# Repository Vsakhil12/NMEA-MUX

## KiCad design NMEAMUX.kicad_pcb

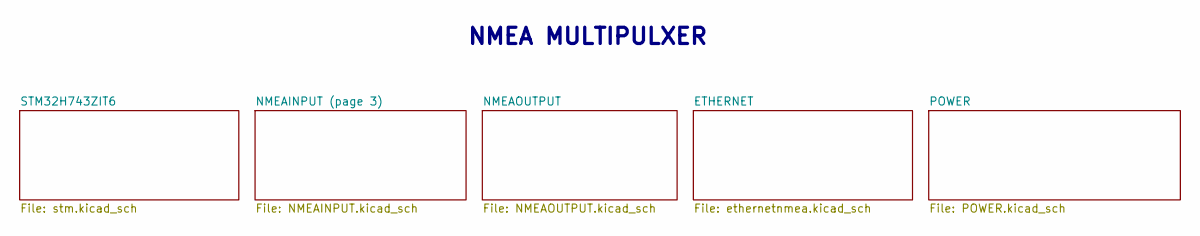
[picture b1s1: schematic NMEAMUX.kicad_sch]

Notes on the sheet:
NMEA MULTIPULXER

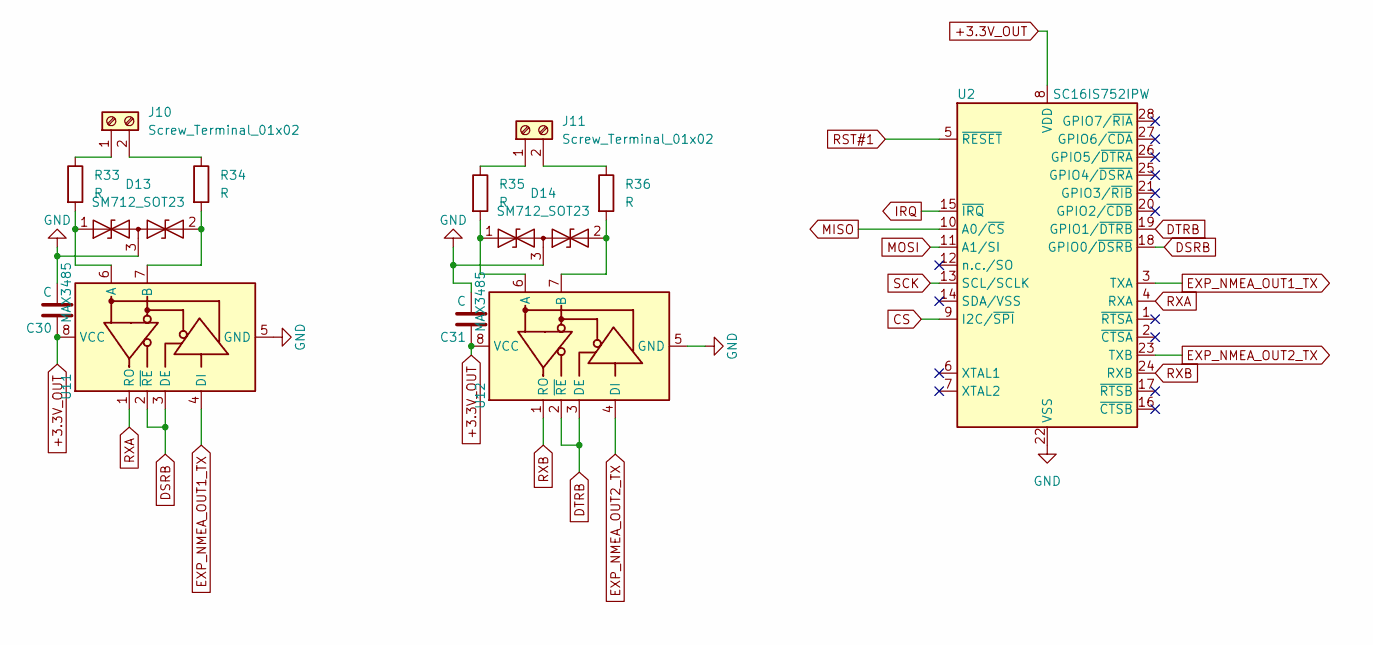
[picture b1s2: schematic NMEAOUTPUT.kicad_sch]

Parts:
C30, C31: C
D13, D14: SM712_SOT23; SOT-23
J10, J11: Screw_Terminal_01x02
R33, R34, R35, R36: R
U2: SC16IS752IPW; TSSOP-28_4.4x9.7mm_P0.65mm
U11, U12: MAX3485; SOIC-8_3.9x4.9mm_P1.27mm

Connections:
+3.3V_OUT: C30.1, C31.1, U2.8 (VDD), U11.8 (VCC), U12.8 (VCC); also elsewhere on the board
CS: U2.9 (I2C/~SPI); also elsewhere on the board
DSRB: U2.18 (GPIO0/~DSRB), U11.2 (~RE), U11.3 (DE)
DTRB: U2.19 (GPIO1/~DTRB), U12.2 (~RE), U12.3 (DE)
EXP_NMEA_OUT1_TX: U2.3 (TXA), U11.4 (DI)
EXP_NMEA_OUT2_TX: U2.23 (TXB), U12.4 (DI)
GND: C30.2, C31.2, D13.3 (common), D14.3 (common), U2.22 (VSS), U11.5 (GND), U12.5 (GND); also elsewhere on the board
IRQ: U2.15 (~IRQ); also elsewhere on the board
MISO: U2.10 (A0/~CS); also elsewhere on the board
MOSI: U2.11 (A1/SI); also elsewhere on the board
unnamed: D13.1 (A1), R33.2, U11.6 (A)
unnamed: D13.2 (A2), R34.2, U11.7 (B)
unnamed: D14.1 (A1), R35.2, U12.6 (A)
unnamed: D14.2 (A2), R36.2, U12.7 (B)
unnamed: J10.1, R33.1
unnamed: J10.2, R34.1
unnamed: J11.1, R35.1
unnamed: J11.2, R36.1
RST#1: U2.5 (~RESET); also elsewhere on the board
RXA: U2.4 (RXA), U11.1 (RO)
RXB: U2.24 (RXB), U12.1 (RO)
SCK: U2.13 (SCL/SCLK); also elsewhere on the board

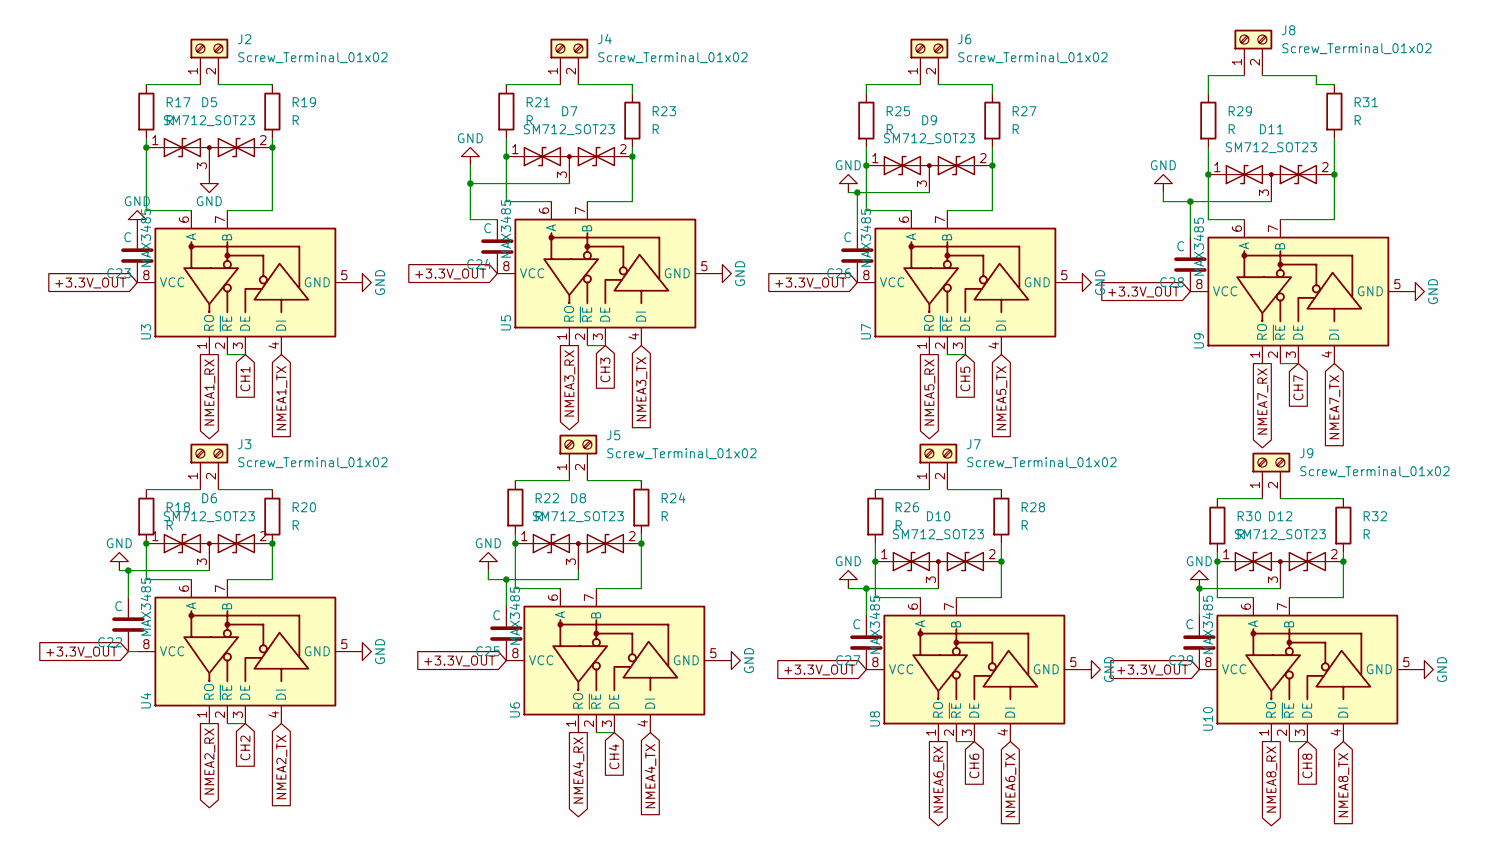
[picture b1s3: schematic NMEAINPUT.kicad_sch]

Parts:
C22, C23, C24, C25, C26, C27, C28, C29: C
D5, D6, D7, D8, D9, D10, D11, D12: SM712_SOT23; SOT-23
J2, J3, J4, J5, J6, J7, J8, J9: Screw_Terminal_01x02
R17, R18, R19, R20, R21, R22, R23, R24, R25, R26, R27, R28, R29, R30, R31, R32: R
U3, U4, U5, U6, U7, U8, U9, U10: MAX3485; SOIC-8_3.9x4.9mm_P1.27mm

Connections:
+3.3V_OUT: C22.1, C23.1, C24.1, C25.1, C26.1, C27.1, C28.1, C29.1, U3.8 (VCC), U4.8 (VCC), U5.8 (VCC), U6.8 (VCC), U7.8 (VCC), U8.8 (VCC), U9.8 (VCC), U10.8 (VCC); also elsewhere on the board
CH1: U3.2 (~RE), U3.3 (DE); also elsewhere on the board
CH2: U4.2 (~RE), U4.3 (DE); also elsewhere on the board
CH3: U5.2 (~RE), U5.3 (DE); also elsewhere on the board
CH4: U6.2 (~RE), U6.3 (DE); also elsewhere on the board
CH5: U7.2 (~RE), U7.3 (DE); also elsewhere on the board
CH6: U8.2 (~RE), U8.3 (DE); also elsewhere on the board
CH7: U9.2 (~RE), U9.3 (DE); also elsewhere on the board
CH8: U10.2 (~RE), U10.3 (DE); also elsewhere on the board
GND: C22.2, C23.2, C24.2, C25.2, C26.2, C27.2, C28.2, C29.2, D5.3 (common), D6.3 (common), D7.3 (common), D8.3 (common), D9.3 (common), D10.3 (common), D11.3 (common), D12.3 (common), U3.5 (GND), U4.5 (GND), U5.5 (GND), U6.5 (GND), U7.5 (GND), U8.5 (GND), U9.5 (GND), U10.5 (GND); also elsewhere on the board
NMEA1_RX: U3.1 (RO); also elsewhere on the board
NMEA1_TX: U3.4 (DI); also elsewhere on the board
NMEA2_RX: U4.1 (RO); also elsewhere on the board
NMEA2_TX: U4.4 (DI); also elsewhere on the board
NMEA3_RX: U5.1 (RO); also elsewhere on the board
NMEA3_TX: U5.4 (DI); also elsewhere on the board
NMEA4_RX: U6.1 (RO); also elsewhere on the board
NMEA4_TX: U6.4 (DI); also elsewhere on the board
NMEA5_RX: U7.1 (RO); also elsewhere on the board
NMEA5_TX: U7.4 (DI); also elsewhere on the board
NMEA6_RX: U8.1 (RO); also elsewhere on the board
NMEA6_TX: U8.4 (DI); also elsewhere on the board
NMEA7_RX: U9.1 (RO); also elsewhere on the board
NMEA7_TX: U9.4 (DI); also elsewhere on the board
NMEA8_RX: U10.1 (RO); also elsewhere on the board
NMEA8_TX: U10.4 (DI); also elsewhere on the board
unnamed: D5.1 (A1), R17.2, U3.6 (A)
unnamed: D5.2 (A2), R19.2, U3.7 (B)
unnamed: D6.1 (A1), R18.2, U4.6 (A)
unnamed: D6.2 (A2), R20.2, U4.7 (B)
unnamed: D7.1 (A1), R21.2, U5.6 (A)
unnamed: D7.2 (A2), R23.2, U5.7 (B)
unnamed: D8.1 (A1), R22.2, U6.6 (A)
unnamed: D8.2 (A2), R24.2, U6.7 (B)
unnamed: D9.1 (A1), R25.2, U7.6 (A)
unnamed: D9.2 (A2), R27.2, U7.7 (B)
unnamed: D10.1 (A1), R26.2, U8.6 (A)
unnamed: D10.2 (A2), R28.2, U8.7 (B)
unnamed: D11.1 (A1), R29.2, U9.6 (A)
unnamed: D11.2 (A2), R31.2, U9.7 (B)
unnamed: D12.1 (A1), R30.2, U10.6 (A)
unnamed: D12.2 (A2), R32.2, U10.7 (B)
unnamed: J2.1, R17.1
unnamed: J2.2, R19.1
unnamed: J3.1, R18.1
unnamed: J3.2, R20.1
unnamed: J4.1, R21.1
unnamed: J4.2, R23.1
unnamed: J5.1, R22.1
unnamed: J5.2, R24.1
unnamed: J6.1, R25.1
unnamed: J6.2, R27.1
unnamed: J7.1, R26.1
unnamed: J7.2, R28.1
unnamed: J8.1, R29.1
unnamed: J8.2, R31.1
unnamed: J9.1, R30.1
unnamed: J9.2, R32.1

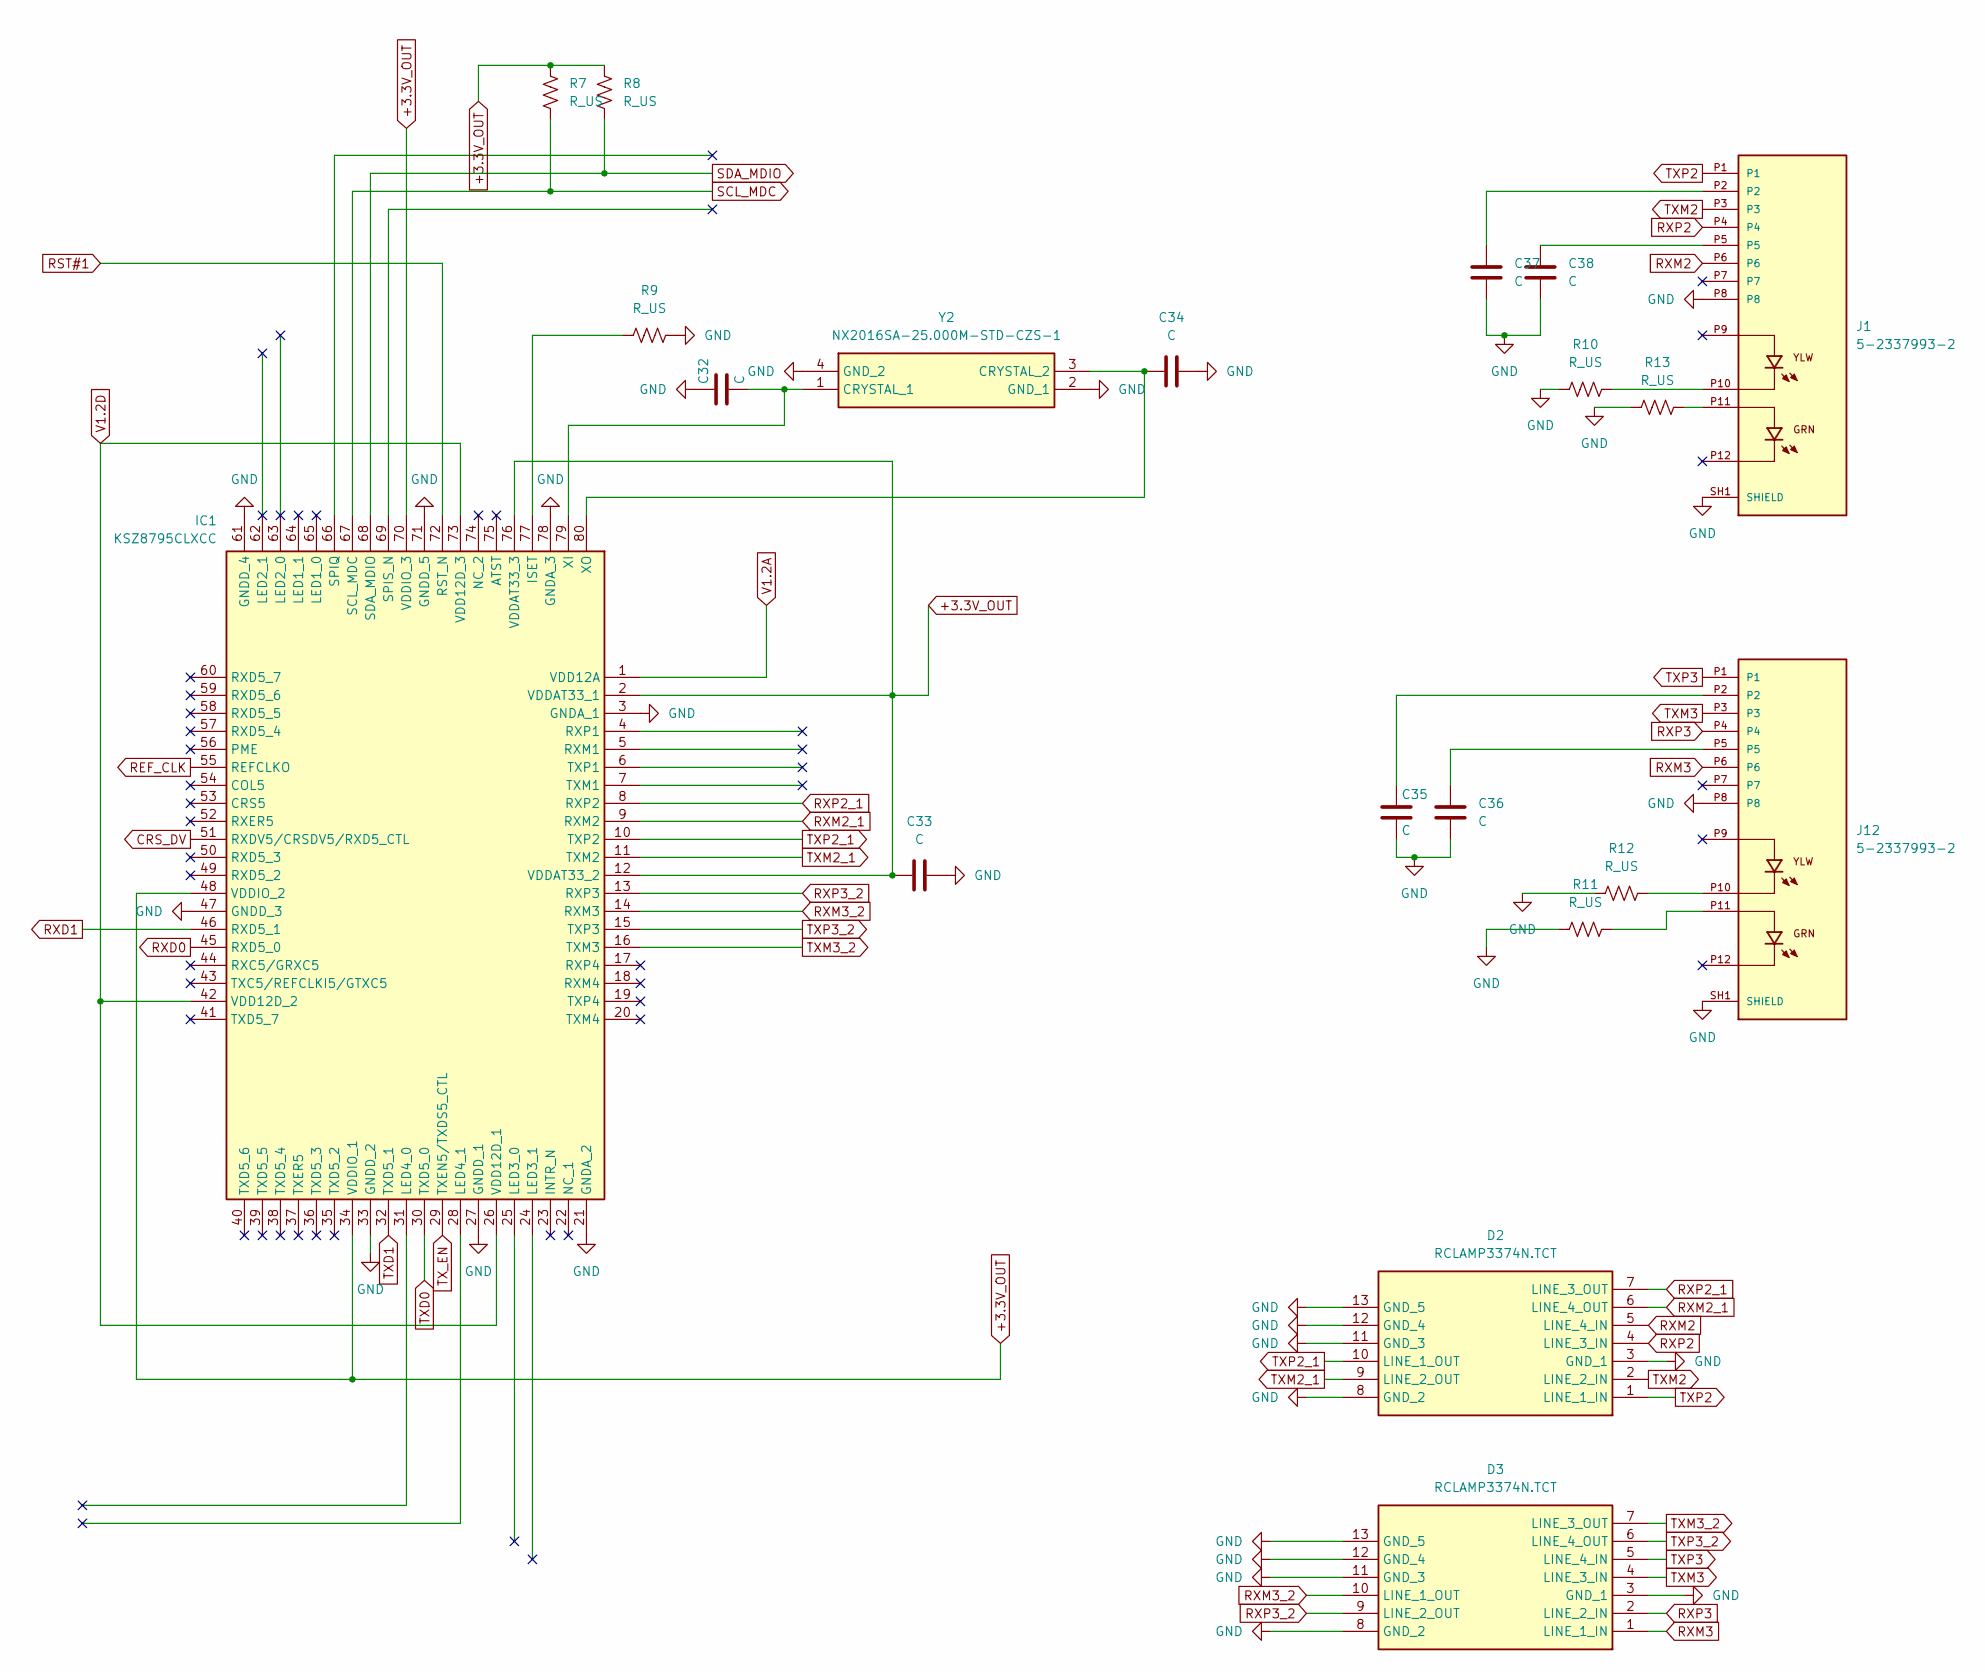
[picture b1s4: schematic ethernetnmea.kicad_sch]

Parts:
C32, C33, C34, C35, C36, C37, C38: C
D2, D3: RCLAMP3374N.TCT; RCLAMP3374NTCT; Manufacturer_Part_Number RCLAMP3374N.TCT; Mouser Part Number 947-RCLAMP3374N.TCT
IC1: KSZ8795CLXCC; QFP40P1200X1200X160-80N; Manufacturer_Part_Number KSZ8795CLXCC; Mouser Part Number 998-KSZ8795CLXCC
J1, J12: 5-2337993-2; TE_5-2337993-2; PARTREV A
R7, R8, R9, R10, R11, R12, R13: R_US
Y2: NX2016SA-25.000M-STD-CZS-1; NX2016SA32MEXS00ACS06465; Manufacturer_Part_Number NX2016SA-25.000M-STD-CZS-1; Mouser Part Number 344-NX2016SA25MSTZS1

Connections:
+3.3V_OUT: C33.1, IC1.2 (VDDAT33_1), IC1.12 (VDDAT33_2), IC1.34 (VDDIO_1), IC1.48 (VDDIO_2), IC1.70 (VDDIO_3), IC1.76 (VDDAT33_3), R7.1, R8.1; also elsewhere on the board
CRS_DV: IC1.51 (RXDV5/CRSDV5/RXD5_CTL); also elsewhere on the board
GND: C32.1, C33.2, C34.2, C35.2, C36.2, C37.2, C38.2, D2.3 (GND_1), D2.8 (GND_2), D2.11 (GND_3), D2.12 (GND_4), D2.13 (GND_5), D3.3 (GND_1), D3.8 (GND_2), D3.11 (GND_3), D3.12 (GND_4), D3.13 (GND_5), IC1.3 (GNDA_1), IC1.21 (GNDA_2), IC1.27 (GNDD_1), IC1.33 (GNDD_2), IC1.47 (GNDD_3), IC1.61 (GNDD_4), IC1.71 (GNDD_5), IC1.78 (GNDA_3), J1.P8, J1.SH1 (SHIELD), J1.SH2 (SHIELD), J12.P8, J12.SH1 (SHIELD), J12.SH2 (SHIELD), R9.2, R10.2, R11.2, R12.2, R13.2, Y2.2 (GND_1), Y2.4 (GND_2); also elsewhere on the board
unnamed: C35.1, J12.P2
unnamed: C36.1, J12.P5
unnamed: C37.1, J1.P2
unnamed: C38.1, J1.P5
unnamed: IC1.77 (ISET), R9.1
unnamed: C32.2, IC1.79 (XI), Y2.1 (CRYSTAL_1)
unnamed: C34.1, IC1.80 (XO), Y2.3 (CRYSTAL_2)
unnamed: J1.P10, R10.1
unnamed: J1.P11, R13.1
unnamed: J12.P10, R12.1
unnamed: J12.P11, R11.1
REF_CLK: IC1.55 (REFCLKO); also elsewhere on the board
RST#1: IC1.72 (RST_N); also elsewhere on the board
RXD0: IC1.45 (RXD5_0); also elsewhere on the board
RXD1: IC1.46 (RXD5_1); also elsewhere on the board
RXM2: D2.5 (LINE_4_IN), J1.P6
RXM2_1: D2.6 (LINE_4_OUT), IC1.9 (RXM2)
RXM3: D3.1 (LINE_1_IN), J12.P6
RXM3_2: D3.10 (LINE_1_OUT), IC1.14 (RXM3)
RXP2: D2.4 (LINE_3_IN), J1.P4
RXP2_1: D2.7 (LINE_3_OUT), IC1.8 (RXP2)
RXP3: D3.2 (LINE_2_IN), J12.P4
RXP3_2: D3.9 (LINE_2_OUT), IC1.13 (RXP3)
SCL_MDC: IC1.67 (SCL_MDC), R7.2; also elsewhere on the board
SDA_MDIO: IC1.68 (SDA_MDIO), R8.2; also elsewhere on the board
TXD0: IC1.30 (TXD5_0); also elsewhere on the board
TXD1: IC1.32 (TXD5_1); also elsewhere on the board
TXM2: D2.2 (LINE_2_IN), J1.P3
TXM2_1: D2.9 (LINE_2_OUT), IC1.11 (TXM2)
TXM3: D3.4 (LINE_3_IN), J12.P3
TXM3_2: D3.7 (LINE_3_OUT), IC1.16 (TXM3)
TXP2: D2.1 (LINE_1_IN), J1.P1
TXP2_1: D2.10 (LINE_1_OUT), IC1.10 (TXP2)
TXP3: D3.5 (LINE_4_IN), J12.P1
TXP3_2: D3.6 (LINE_4_OUT), IC1.15 (TXP3)
TX_EN: IC1.29 (TXEN5/TXDS5_CTL); also elsewhere on the board
V1.2A: IC1.1 (VDD12A); also elsewhere on the board
V1.2D: IC1.26 (VDD12D_1), IC1.42 (VDD12D_2), IC1.73 (VDD12D_3); also elsewhere on the board

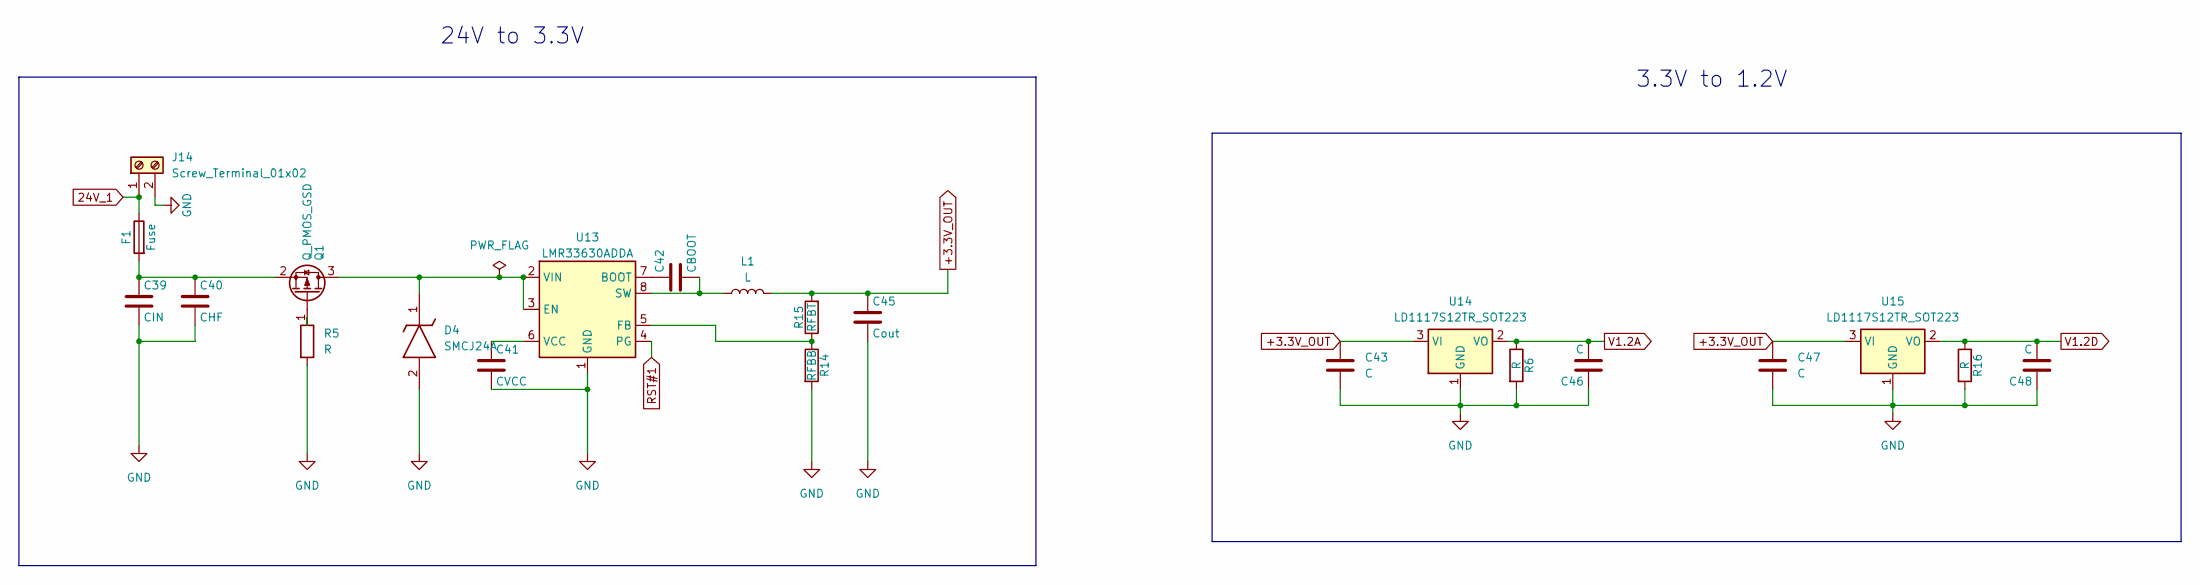
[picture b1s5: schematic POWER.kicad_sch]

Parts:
C39: CIN
C40: CHF
C41: CVCC
C42: CBOOT
C43, C46, C47, C48: C
C45: Cout
D4: SMCJ24A; DIOM7959X262N; Manufacturer_Part_Number SMCJ24A; Mouser Part Number 78-SMCJ24A
F1: Fuse
J14: Screw_Terminal_01x02
L1: L
Q1: Q_PMOS_GSD
R5, R6, R16: R
R14: RFBB
R15: RFBT
U13: LMR33630ADDA; Texas_HSOP-8-1EP_3.9x4.9mm_P1.27mm_ThermalVias
U14, U15: LD1117S12TR_SOT223; SOT-223-3_TabPin2

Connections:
24V_1: F1.1, J14.1
+3.3V_OUT: C43.2, C45.1, C47.2, L1.2, R15.2, U14.3 (VI), U15.3 (VI); also elsewhere on the board
GND: C39.2, C40.2, C41.2, C43.1, C45.2, C46.1, C47.1, C48.1, D4.2 (A), J14.2, R5.2, R6.2, R14.2, R16.2, U13.1 (GND), U13.9 (GND), U14.1 (GND), U15.1 (GND); also elsewhere on the board
unnamed: D4.1 (K), Q1.3 (D), U13.2 (VIN), U13.3 (EN)
unnamed: Q1.1 (G), R5.1
unnamed: C39.1, C40.1, F1.2, Q1.2 (S)
unnamed: C42.1, U13.7 (BOOT)
unnamed: R14.1, R15.1, U13.5 (FB)
unnamed: C42.2, L1.1, U13.8 (SW)
unnamed: C41.1, U13.6 (VCC)
RST#1: U13.4 (PG); also elsewhere on the board
V1.2A: C46.2, R6.1, U14.2 (VO); also elsewhere on the board
V1.2D: C48.2, R16.1, U15.2 (VO); also elsewhere on the board

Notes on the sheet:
3.3V to 1.2V
24V to 3.3V

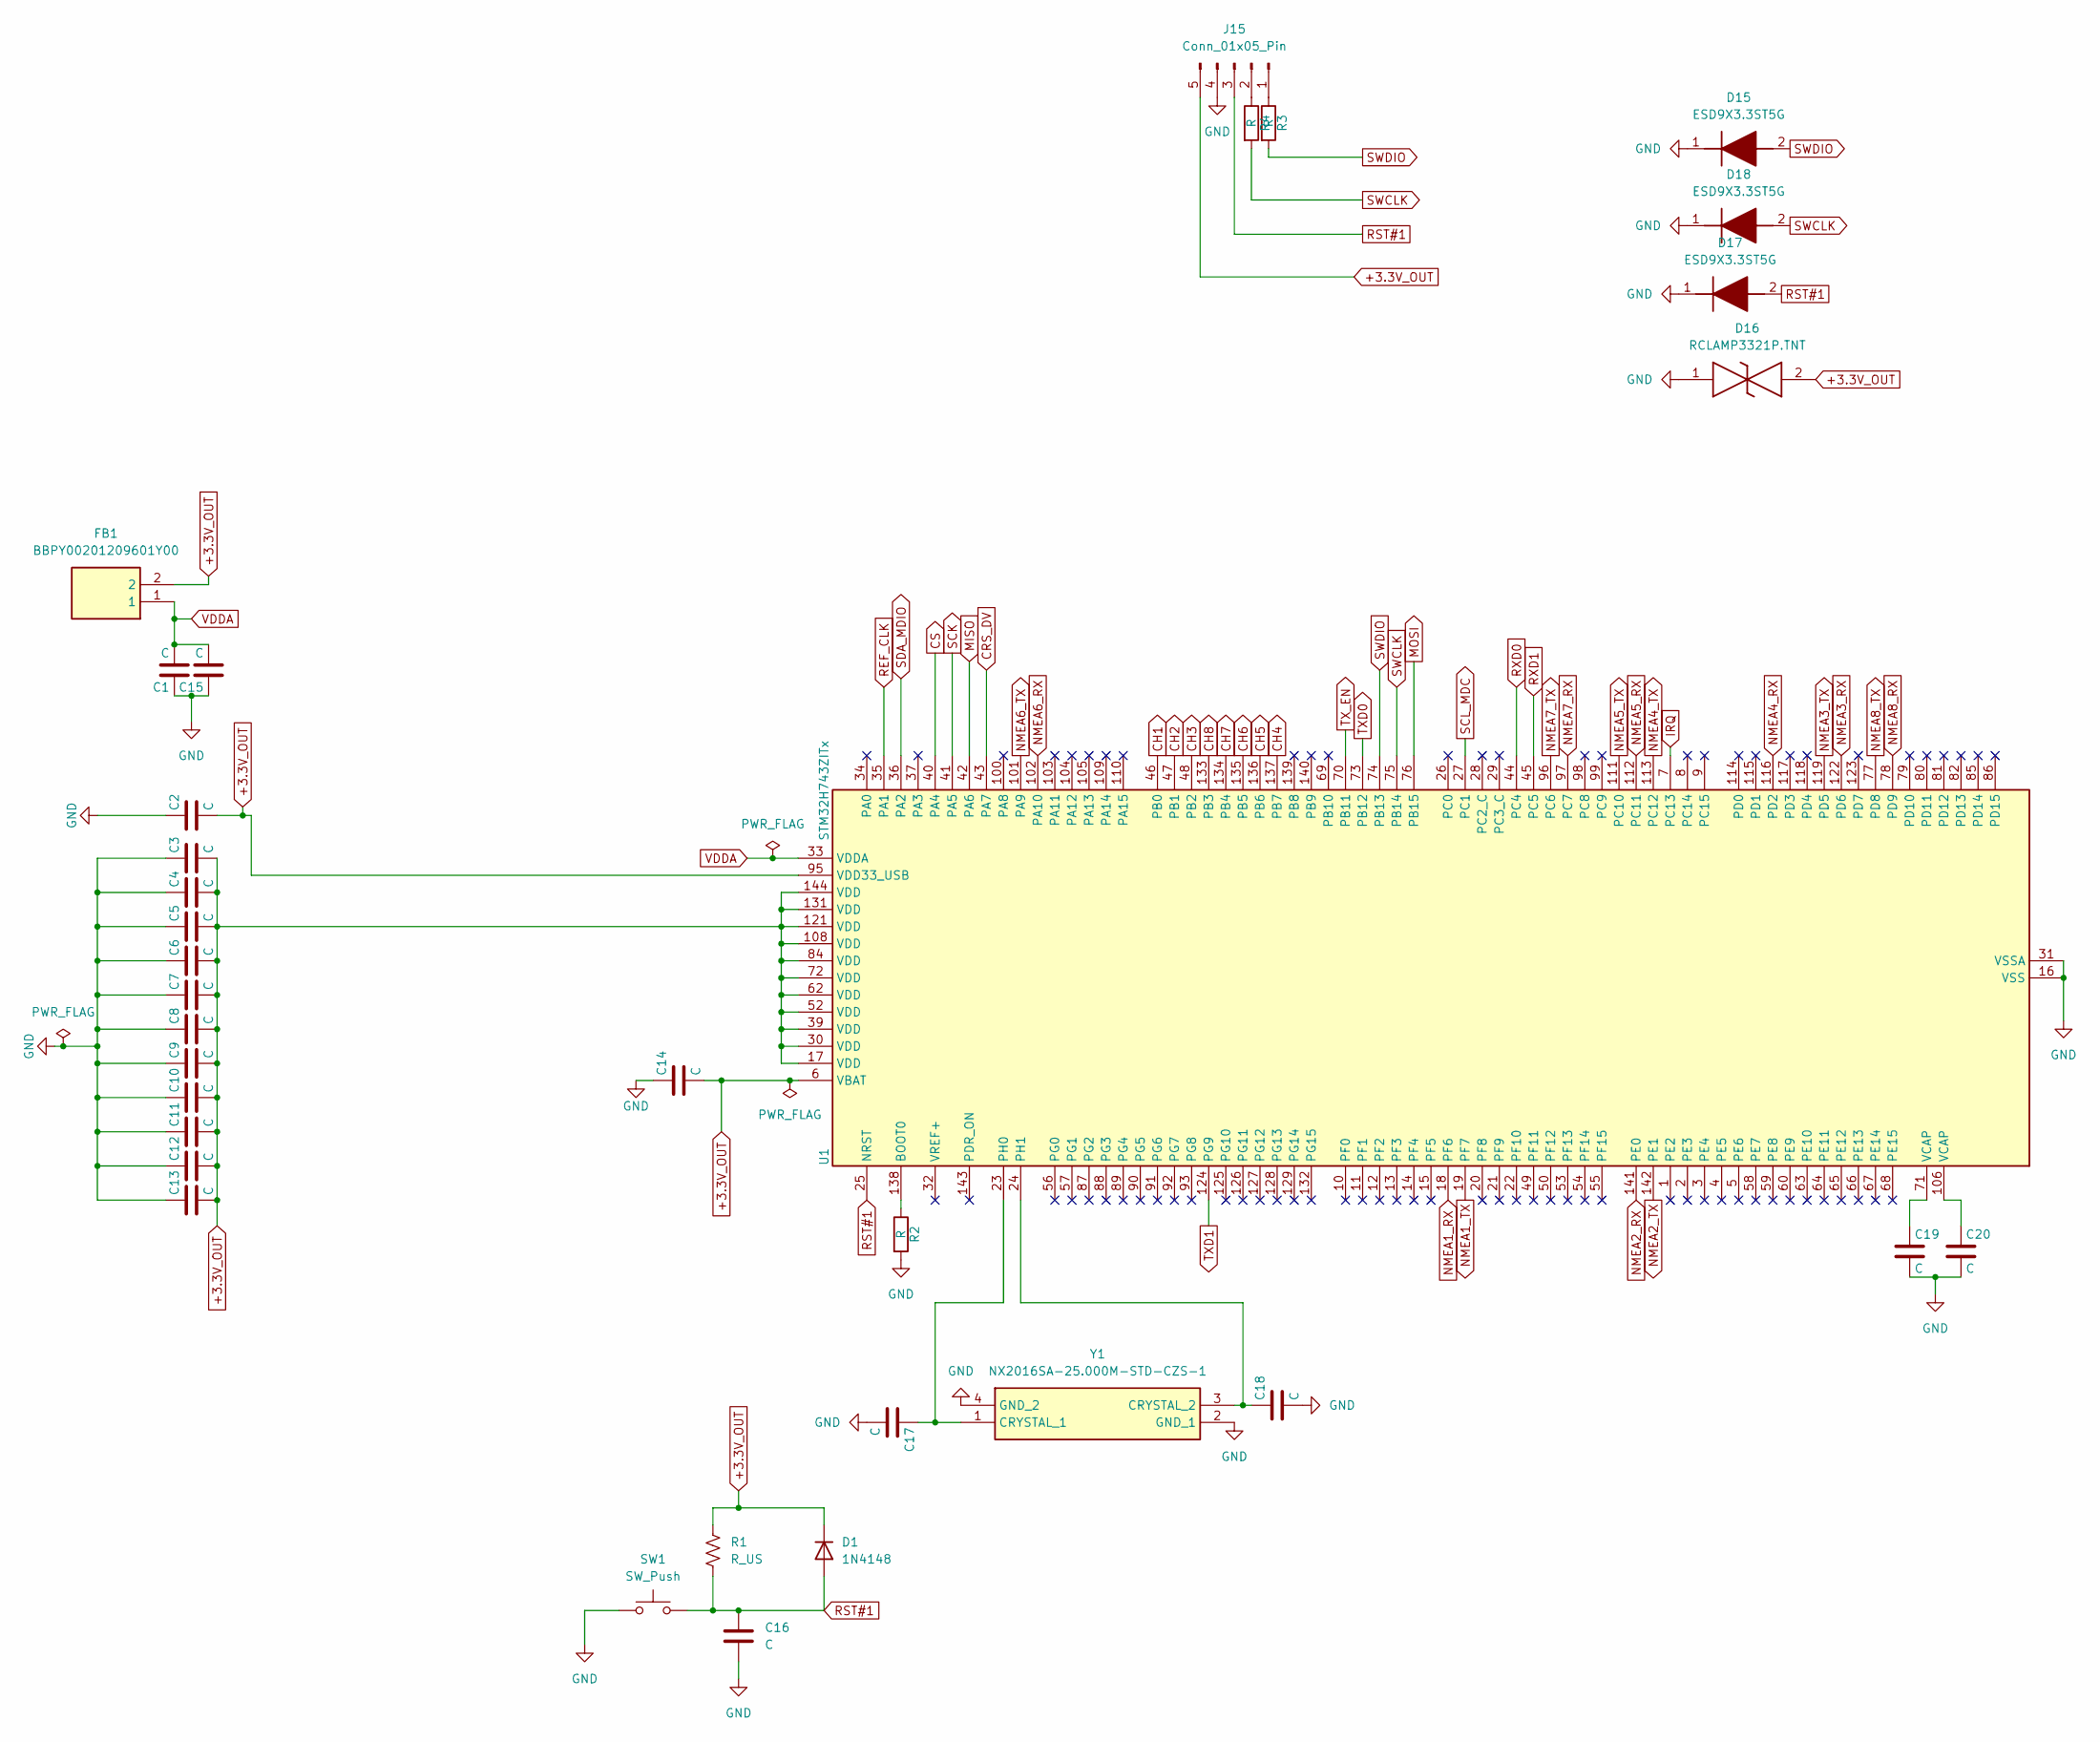
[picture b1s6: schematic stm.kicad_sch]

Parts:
C1, C2, C3, C4, C5, C6, C7, C8, C9, C10, C11, C12, C13, C14, C15, C16, C17, C18, C19, C20: C
D1: 1N4148; D_DO-35_SOD27_P7.62mm_Horizontal
D15, D17, D18: ESD9X3.3ST5G; SODFL1006X43N; Manufacturer_Part_Number ESD9X3.3ST5G; Mouser Part Number 863-ESD9X3.3ST5G
D16: RCLAMP3321P.TNT; RCLAMP3321PTNT; Manufacturer_Part_Number RCLAMP3321P.TNT; Mouser Part Number 947-RCLAMP3321P.TNT
FB1: BBPY00201209601Y00; BEADC2012X110N; Manufacturer_Part_Number BBPY00201209601Y00; Mouser Part Number 603-BBPY201209601Y00
J15: Conn_01x05_Pin
R1: R_US
R2, R3, R4: R
SW1: SW_Push
U1: STM32H743ZITx; LQFP-144_20x20mm_P0.5mm
Y1: NX2016SA-25.000M-STD-CZS-1; NX2016SA32MEXS00ACS06465; Manufacturer_Part_Number NX2016SA-25.000M-STD-CZS-1; Mouser Part Number 344-NX2016SA25MSTZS1

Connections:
+3.3V_OUT: C2.2, C3.2, C4.2, C5.2, C6.2, C7.2, C8.2, C9.2, C10.2, C11.2, C12.2, C13.2, C14.2, D1.1 (K), D16.2, FB1.2, J15.5, R1.1, U1.6 (VBAT), U1.17 (VDD), U1.30 (VDD), U1.39 (VDD), U1.52 (VDD), U1.62 (VDD), U1.72 (VDD), U1.84 (VDD), U1.95 (VDD33_USB), U1.108 (VDD), U1.121 (VDD), U1.131 (VDD), U1.144 (VDD); also elsewhere on the board
CH1: U1.46 (PB0); also elsewhere on the board
CH2: U1.47 (PB1); also elsewhere on the board
CH3: U1.48 (PB2); also elsewhere on the board
CH4: U1.137 (PB7); also elsewhere on the board
CH5: U1.136 (PB6); also elsewhere on the board
CH6: U1.135 (PB5); also elsewhere on the board
CH7: U1.134 (PB4); also elsewhere on the board
CH8: U1.133 (PB3); also elsewhere on the board
CRS_DV: U1.43 (PA7); also elsewhere on the board
CS: U1.40 (PA4); also elsewhere on the board
GND: C1.1, C2.1, C3.1, C4.1, C5.1, C6.1, C7.1, C8.1, C9.1, C10.1, C11.1, C12.1, C13.1, C14.1, C15.1, C16.2, C17.2, C18.2, C19.2, C20.2, D15.1 (K), D16.1, D17.1 (K), D18.1 (K), J15.4, R2.2, SW1.1, U1.16 (VSS), U1.31 (VSSA), U1.38 (VSS), U1.51 (VSS), U1.61 (VSS), U1.83 (VSS), U1.94 (VSS), U1.107 (VSS), U1.120 (VSS), U1.130 (VSS), Y1.2 (GND_1), Y1.4 (GND_2); also elsewhere on the board
IRQ: U1.7 (PC13); also elsewhere on the board
MISO: U1.42 (PA6); also elsewhere on the board
MOSI: U1.76 (PB15); also elsewhere on the board
NMEA1_RX: U1.18 (PF6); also elsewhere on the board
NMEA1_TX: U1.19 (PF7); also elsewhere on the board
NMEA2_RX: U1.141 (PE0); also elsewhere on the board
NMEA2_TX: U1.142 (PE1); also elsewhere on the board
NMEA3_RX: U1.122 (PD6); also elsewhere on the board
NMEA3_TX: U1.119 (PD5); also elsewhere on the board
NMEA4_RX: U1.116 (PD2); also elsewhere on the board
NMEA4_TX: U1.113 (PC12); also elsewhere on the board
NMEA5_RX: U1.112 (PC11); also elsewhere on the board
NMEA5_TX: U1.111 (PC10); also elsewhere on the board
NMEA6_RX: U1.102 (PA10); also elsewhere on the board
NMEA6_TX: U1.101 (PA9); also elsewhere on the board
NMEA7_RX: U1.97 (PC7); also elsewhere on the board
NMEA7_TX: U1.96 (PC6); also elsewhere on the board
NMEA8_RX: U1.78 (PD9); also elsewhere on the board
NMEA8_TX: U1.77 (PD8); also elsewhere on the board
unnamed: C19.1, U1.71 (VCAP)
unnamed: C20.1, U1.106 (VCAP)
unnamed: J15.1, R3.1
unnamed: J15.2, R4.1
unnamed: R2.1, U1.138 (BOOT0)
unnamed: C17.1, U1.23 (PH0), Y1.1 (CRYSTAL_1)
unnamed: C18.1, U1.24 (PH1), Y1.3 (CRYSTAL_2)
REF_CLK: U1.35 (PA1); also elsewhere on the board
RST#1: C16.1, D1.2 (A), D17.2 (A), J15.3, R1.2, SW1.2, U1.25 (NRST); also elsewhere on the board
RXD0: U1.44 (PC4); also elsewhere on the board
RXD1: U1.45 (PC5); also elsewhere on the board
SCK: U1.41 (PA5); also elsewhere on the board
SCL_MDC: U1.27 (PC1); also elsewhere on the board
SDA_MDIO: U1.36 (PA2); also elsewhere on the board
SWCLK: D18.2 (A), R4.2, U1.75 (PB14)
SWDIO: D15.2 (A), R3.2, U1.74 (PB13)
TXD0: U1.73 (PB12); also elsewhere on the board
TXD1: U1.124 (PG9); also elsewhere on the board
TX_EN: U1.70 (PB11); also elsewhere on the board
VDDA: C1.2, C15.2, FB1.1, U1.33 (VDDA)

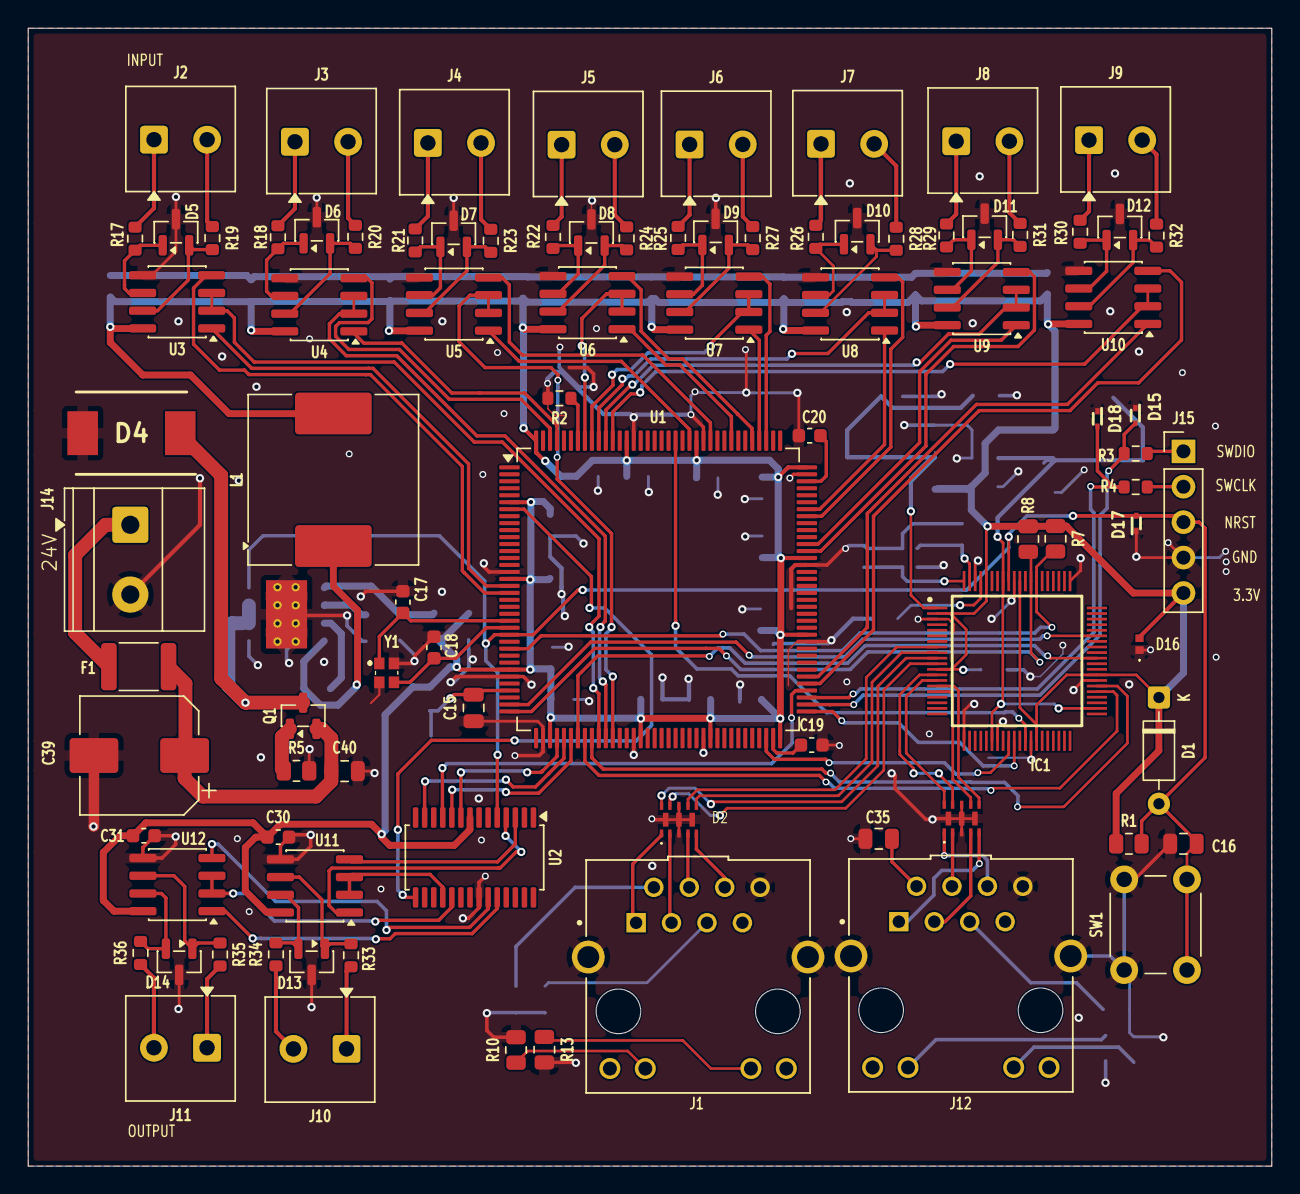
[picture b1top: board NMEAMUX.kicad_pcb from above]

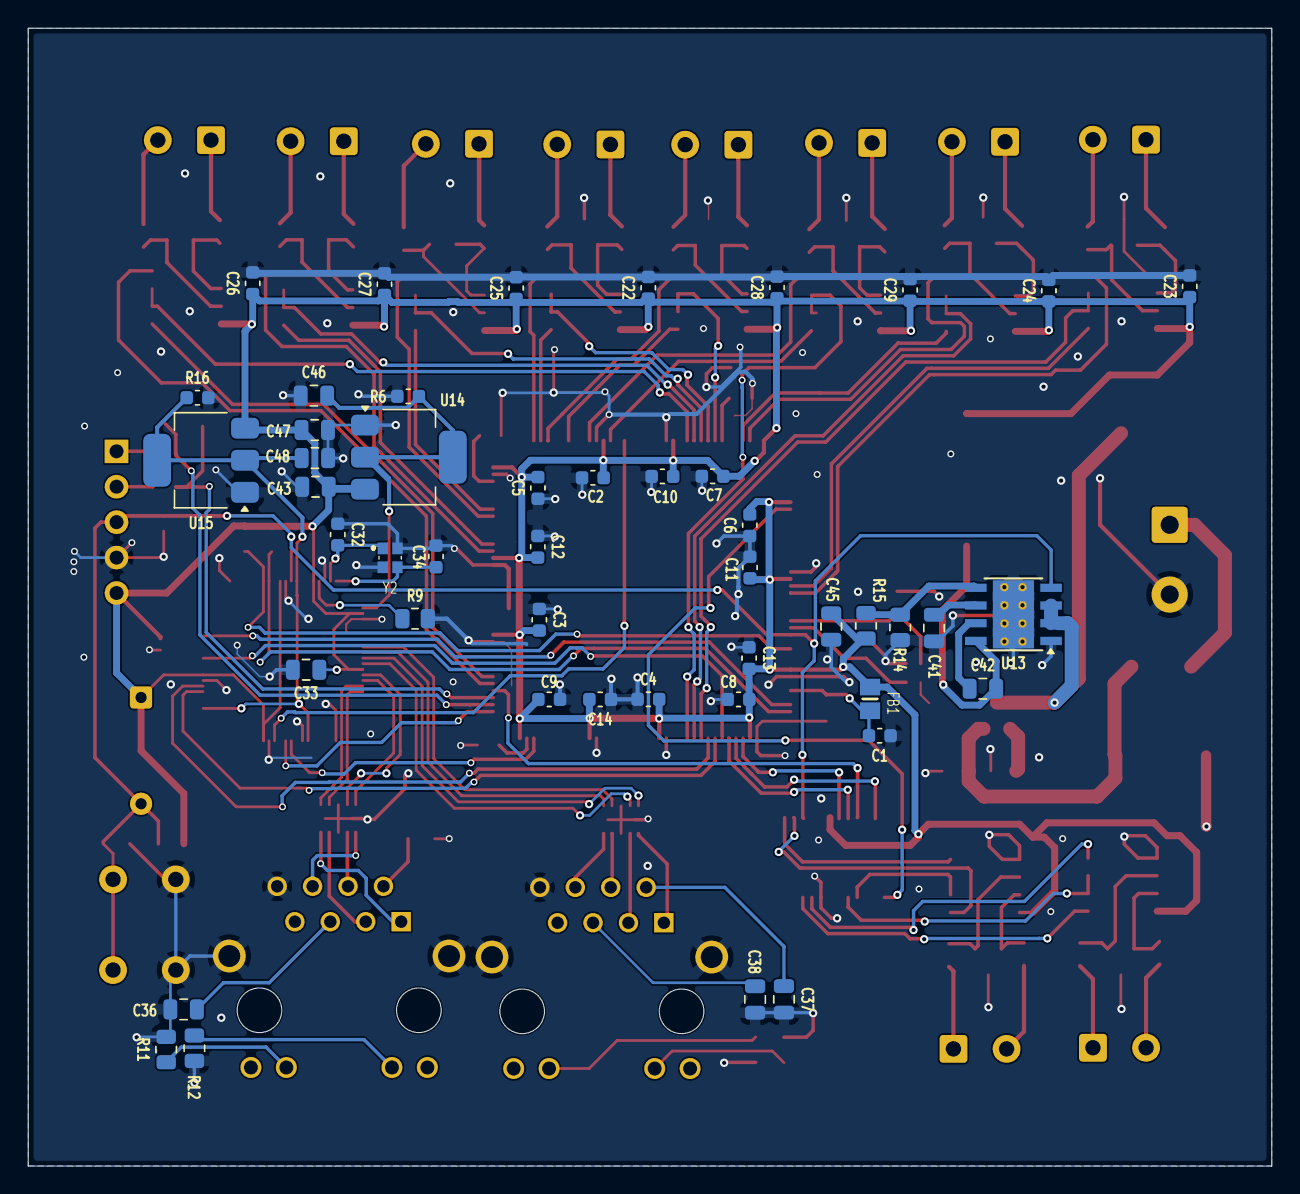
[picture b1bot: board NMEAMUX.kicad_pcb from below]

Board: 2 copper layers, 89.2 x 81.6 mm, 137 parts (47 on the bottom side), 134 nets.
